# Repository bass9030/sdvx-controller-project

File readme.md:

## SDVX-Controller-Project
사볼콘을 사고 싶지만 돈이 없는 학생이 사볼콘을 만들기 위해 똥꼬쇼를 하는 레포

### 진행상황
* 사볼콘 상판 제작 완료 (24.8.3.)
* 메인 PCB, 엔코더 거치용 PCB 제작 완료 (24.8.5.)
* PCB 주문 (24.8.5.) / 설계 한번 잘못해서 5$ 날림 ㅅㅂ
* PCB 전자부품 주문(24.8.6.)
* MDF 재단 주문제작및 기타 부속 주문(24.8.9.)

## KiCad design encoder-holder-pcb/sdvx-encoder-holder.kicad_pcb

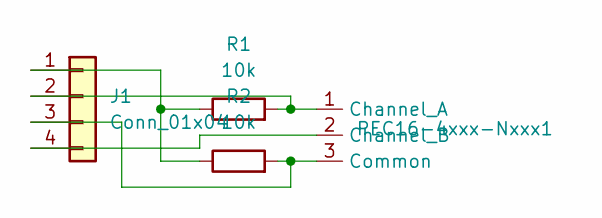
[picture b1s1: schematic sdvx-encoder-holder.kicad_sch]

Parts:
J1: Conn_01x04; JST_XH_B4B-XH-A_1x04_P2.50mm_Vertical
PEC16-4xxx-Nxxx1: PEC16-4XXXF-SXXXX_16X17P3_BRN
R1, R2: 10k; R_0805_2012Metric_Pad1.20x1.40mm_HandSolder

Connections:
unnamed: J1.1, R1.1, R2.1
unnamed: J1.2, PEC16-4xxx-Nxxx1.1 (Channel_A), R1.2
unnamed: J1.3, PEC16-4xxx-Nxxx1.3 (Common), R2.2
unnamed: J1.4, PEC16-4xxx-Nxxx1.2 (Channel_B)

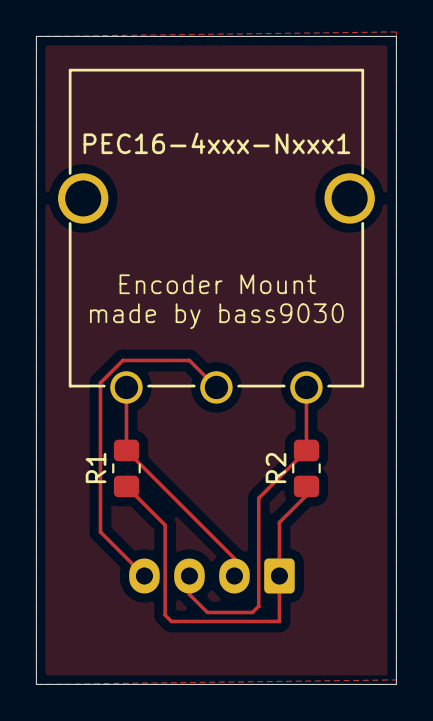
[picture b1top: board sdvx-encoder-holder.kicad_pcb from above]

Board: 2 copper layers, 20.0 x 36.0 mm, 4 parts (1 on the bottom side), 4 nets.

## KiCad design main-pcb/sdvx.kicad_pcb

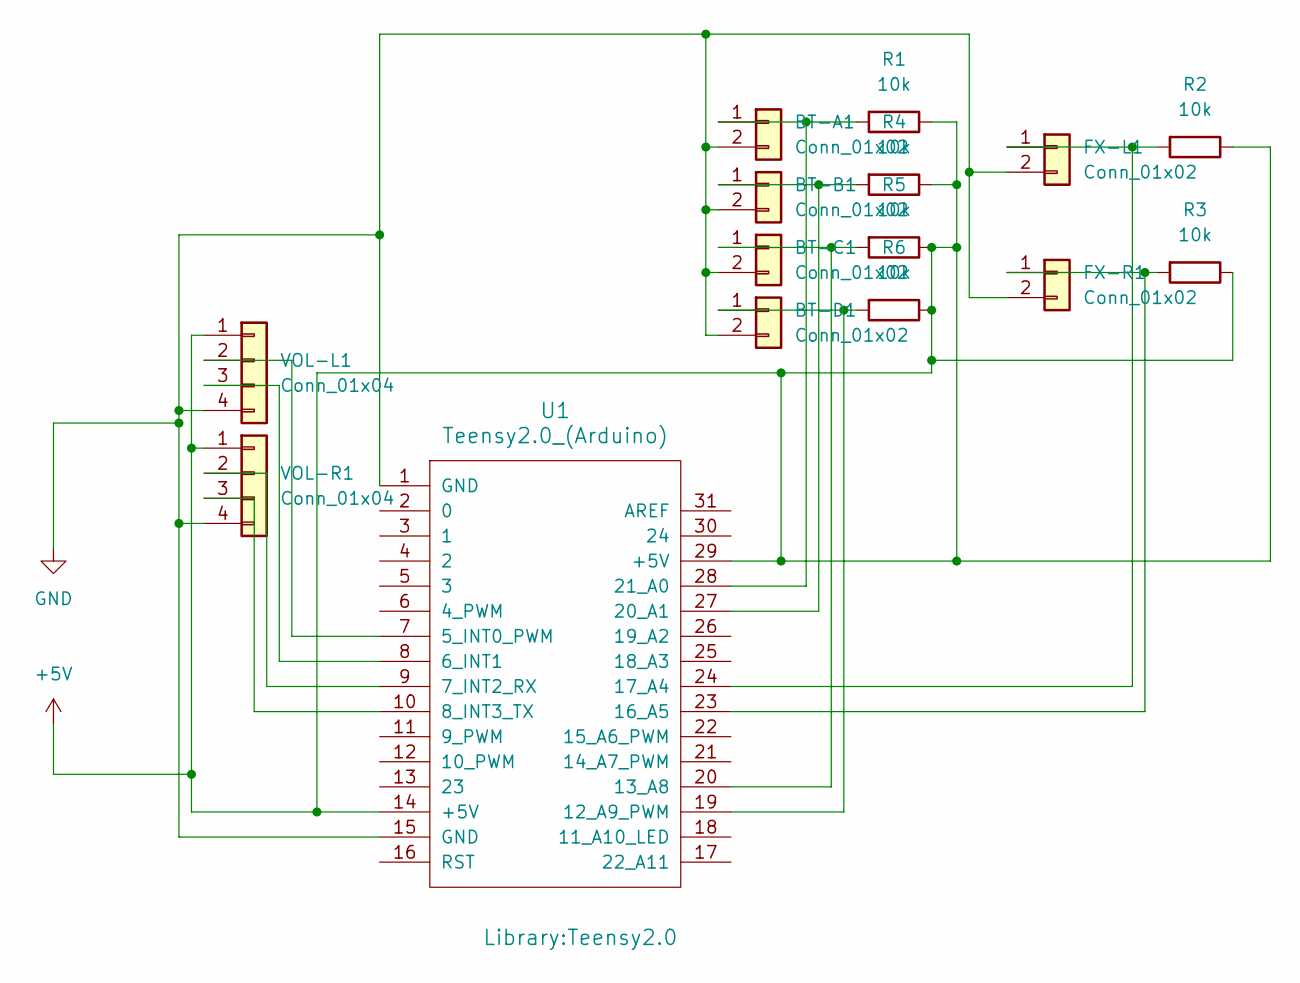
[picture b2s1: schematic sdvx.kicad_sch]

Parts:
BT-A1: Conn_01x02; JST_XH_B2B-XH-A_1x02_P2.50mm_Vertical
BT-B1: Conn_01x02; JST_XH_B2B-XH-A_1x02_P2.50mm_Vertical
BT-C1: Conn_01x02; JST_XH_B2B-XH-A_1x02_P2.50mm_Vertical
BT-D1: Conn_01x02; JST_XH_B2B-XH-A_1x02_P2.50mm_Vertical
FX-L1: Conn_01x02; JST_XH_B2B-XH-A_1x02_P2.50mm_Vertical
FX-R1: Conn_01x02; JST_XH_B2B-XH-A_1x02_P2.50mm_Vertical
R1, R2, R3, R4, R5, R6: 10k; R_0805_2012Metric_Pad1.20x1.40mm_HandSolder
U1: Teensy2.0_(Arduino); Teensy2.0
VOL-L1: Conn_01x04; JST_XH_B4B-XH-A_1x04_P2.50mm_Vertical
VOL-R1: Conn_01x04; JST_XH_B4B-XH-A_1x04_P2.50mm_Vertical

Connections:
+5V: R1.1, R2.1, R3.1, R4.1, R5.1, R6.1, U1.14 (+5V), U1.29 (+5V), VOL-L1.1, VOL-R1.1
GND: BT-A1.2, BT-B1.2, BT-C1.2, BT-D1.2, FX-L1.2, FX-R1.2, U1.1 (GND), U1.15 (GND), VOL-L1.4, VOL-R1.4
unnamed: BT-A1.1, R1.2, U1.28 (21_A0)
unnamed: BT-B1.1, R4.2, U1.27 (20_A1)
unnamed: BT-C1.1, R5.2, U1.20 (13_A8)
unnamed: BT-D1.1, R6.2, U1.19 (12_A9_PWM)
unnamed: FX-L1.1, R2.2, U1.24 (17_A4)
unnamed: FX-R1.1, R3.2, U1.23 (16_A5)
unnamed: U1.7 (5_INT0_PWM), VOL-L1.2
unnamed: U1.8 (6_INT1), VOL-L1.3
unnamed: U1.9 (7_INT2_RX), VOL-R1.2
unnamed: U1.10 (8_INT3_TX), VOL-R1.3

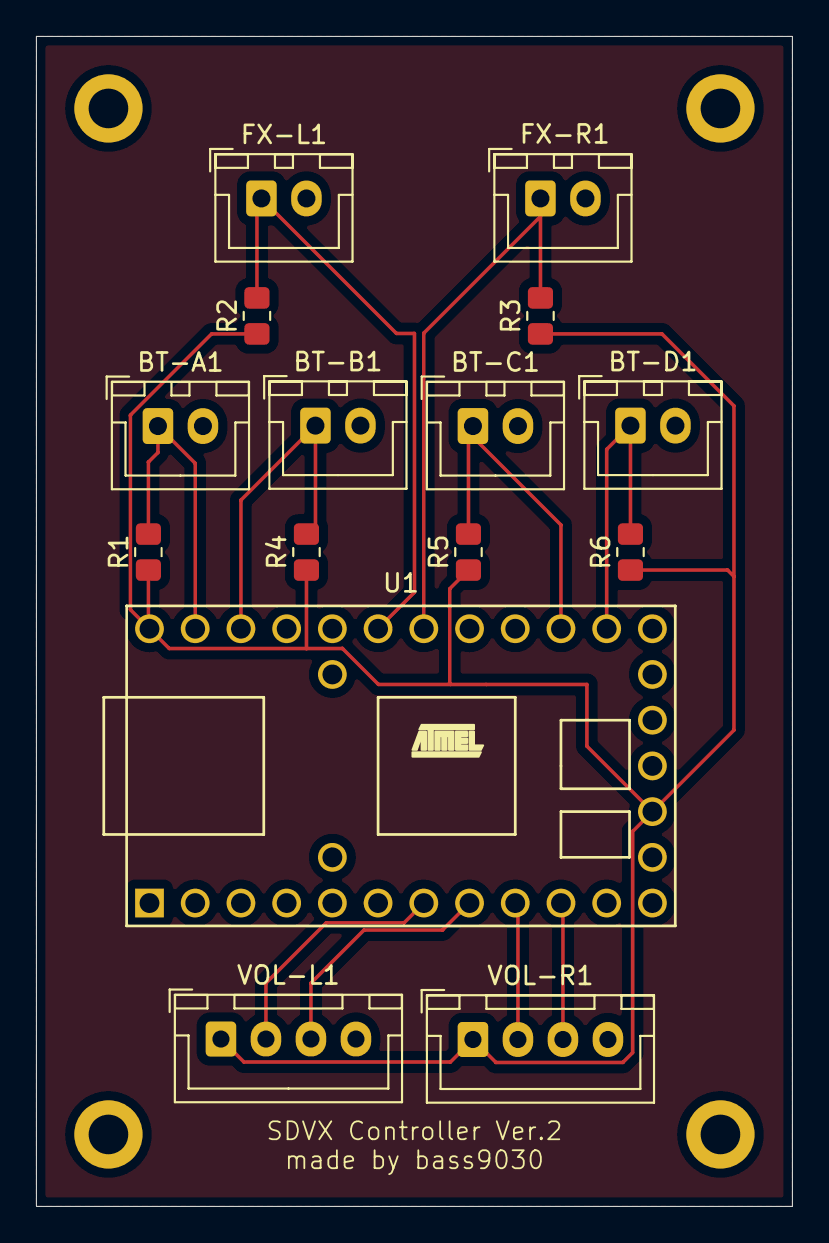
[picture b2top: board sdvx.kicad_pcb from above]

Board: 2 copper layers, 42.0 x 65.0 mm, 15 parts (0 on the bottom side), 12 nets.

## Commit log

2024-08-04 메인 컨트롤러 pcb, 엔코더 홀더 pcb 제작 완료
2024-08-04 readme 추가
2024-08-07 3d 모델링 추가, pcb 회로 백업 파일 제거
2024-08-09 update readme
    제단는 ㅅㅂ 신사 만드냐
